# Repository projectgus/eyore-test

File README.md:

# Eyore-Test

A hardware design for running automated tests against the esp-open-rtos ESP8266-based software framework.

# Major Components

* 2x ESP-12E ESP8266 processor modules, to run tests on. Named A & B.
* 1x STM32F072C8 Cortex M0 microcontroller - acts as USB serial for programming & monitoring, also provides a "programmable peripheral" to test against.
* Host computer with esp-open-rtos source tree, including host test program (`test_runner.py`).

# Cost

Aim is for total BOM cost under $12US for small quantities, all inclusive.

# Functional Description

## Programming/Initialisation

STM32F072 acts as USB device (dual CDC ACM serial port). STM32 USART1 connects to ESP A's TX/RX pins, USART2 to ESP B TX/RX pins.

Other STM32 I/O pins are wired to drive RESET and GPIO0 on both ESP A & ESP B. This allows the STM32 to reset the ESPs & select either serial bootloading or normal operation.

The USB CDC interface provides a "NodeMCU-compatible" reset protocol that works with esptool.py - asserting DTR pulls down GPIO0, asserting RTS pulls down RESET, but asserting both DTR and RTS together does nothing.

## ESP A / ESP B Connections

These connections match the "dual" configuration mentioned in the esp-open-rtos test_setup docs. These allow the ESPs to interact with each other during tests.

This part of the test setup can be reproduced on a breadboard fairly easily.

ESP A & B have the following interconncted pins, all via 220 ohm resistors for short circuit protection:

ESP A | ESP B | Function
----- | ------  --------
2     | 2     |
4     | 4     |
5     | 5     |
12    | 12    |
13    | 15    | ESP UART RX/TX "swapped"
15    | 13    | ESP UART TX/RX "swapped"
14    | 14    |

Note that GPIOs on ESP A are also connected to the STM32.

## ESP A / STM32 Connections

To allow peripheral testing between ESP A and an independent microcontroller, some STM32 peripherals are connected to ESP A peripherals:

ESP A Interface | ESP GPIOs              | STM32 Interface | ESP Pins
--------------- | ---------------------- | ---------------- | ----------------
Software i2c    | 4, 5                   | I2C1             | PB6, PB7 [1]
HSPI            | 12-15                  | SPI1             | PA4-PA7
I2S Input       | 14(WS),13(BCK),12(DAT) | I2S1             | PA15, PB3, PB5
I2S Output      | 2(WS),3(DAT),14(CLK)   | N/A (bit-bang)   | PB11, PA9, PA4 [2]
SPI (flash intf)|                        | SPI2             | PB12..PB15 [3]
ADC (TOUT)      | TOUT                   | GPIO (bit-bang)  | PA0 & PB4 [4]

[1] I2C1 slave is the only STM32 interface enabled after reset, and is the protocol used for the ESP itself to configure the STM32 as a "programmable peripheral".

[2] ESP I2S output is not wired to a I2S peripheral on the STM32. However STM32 can bit-bang reading of the I2S output (at slow clock speeds).

[3] Not used due to hardware bug: On Rev 1.0 of eyore-test the SPI2 NSS pin (slave select) is wired to the CS line of the ESP module, which is the CS line for the ESP's SPI flash. The other SPI2 NSS pin is not connected in this revision.

[4] TOUT pin is connected directly to STM ADC pin PA0. TOUT is also connected to PB4 via an RC network, so PB4 can be used as a low-fi DAC, PWMing a voltage for the ADC to read.

## Programmable Peripheral Interface

As part of each test, ESP A can configure the STM32 peripherals via the I2C interface.

Actual I2C protocol/register details are TBD, likely to be incremental features.

# STM32 Firmware

STM32 has a USB DFU bootloader in ROM. "Flash" button and jumper are provided to access this bootloader on power-on. SWD port is also provided for external programming/debugging if necessary.

# Name

I've seen esp-open-rtos abbreviated to "e-o-r", and I tend to read that as "Eyore". :)

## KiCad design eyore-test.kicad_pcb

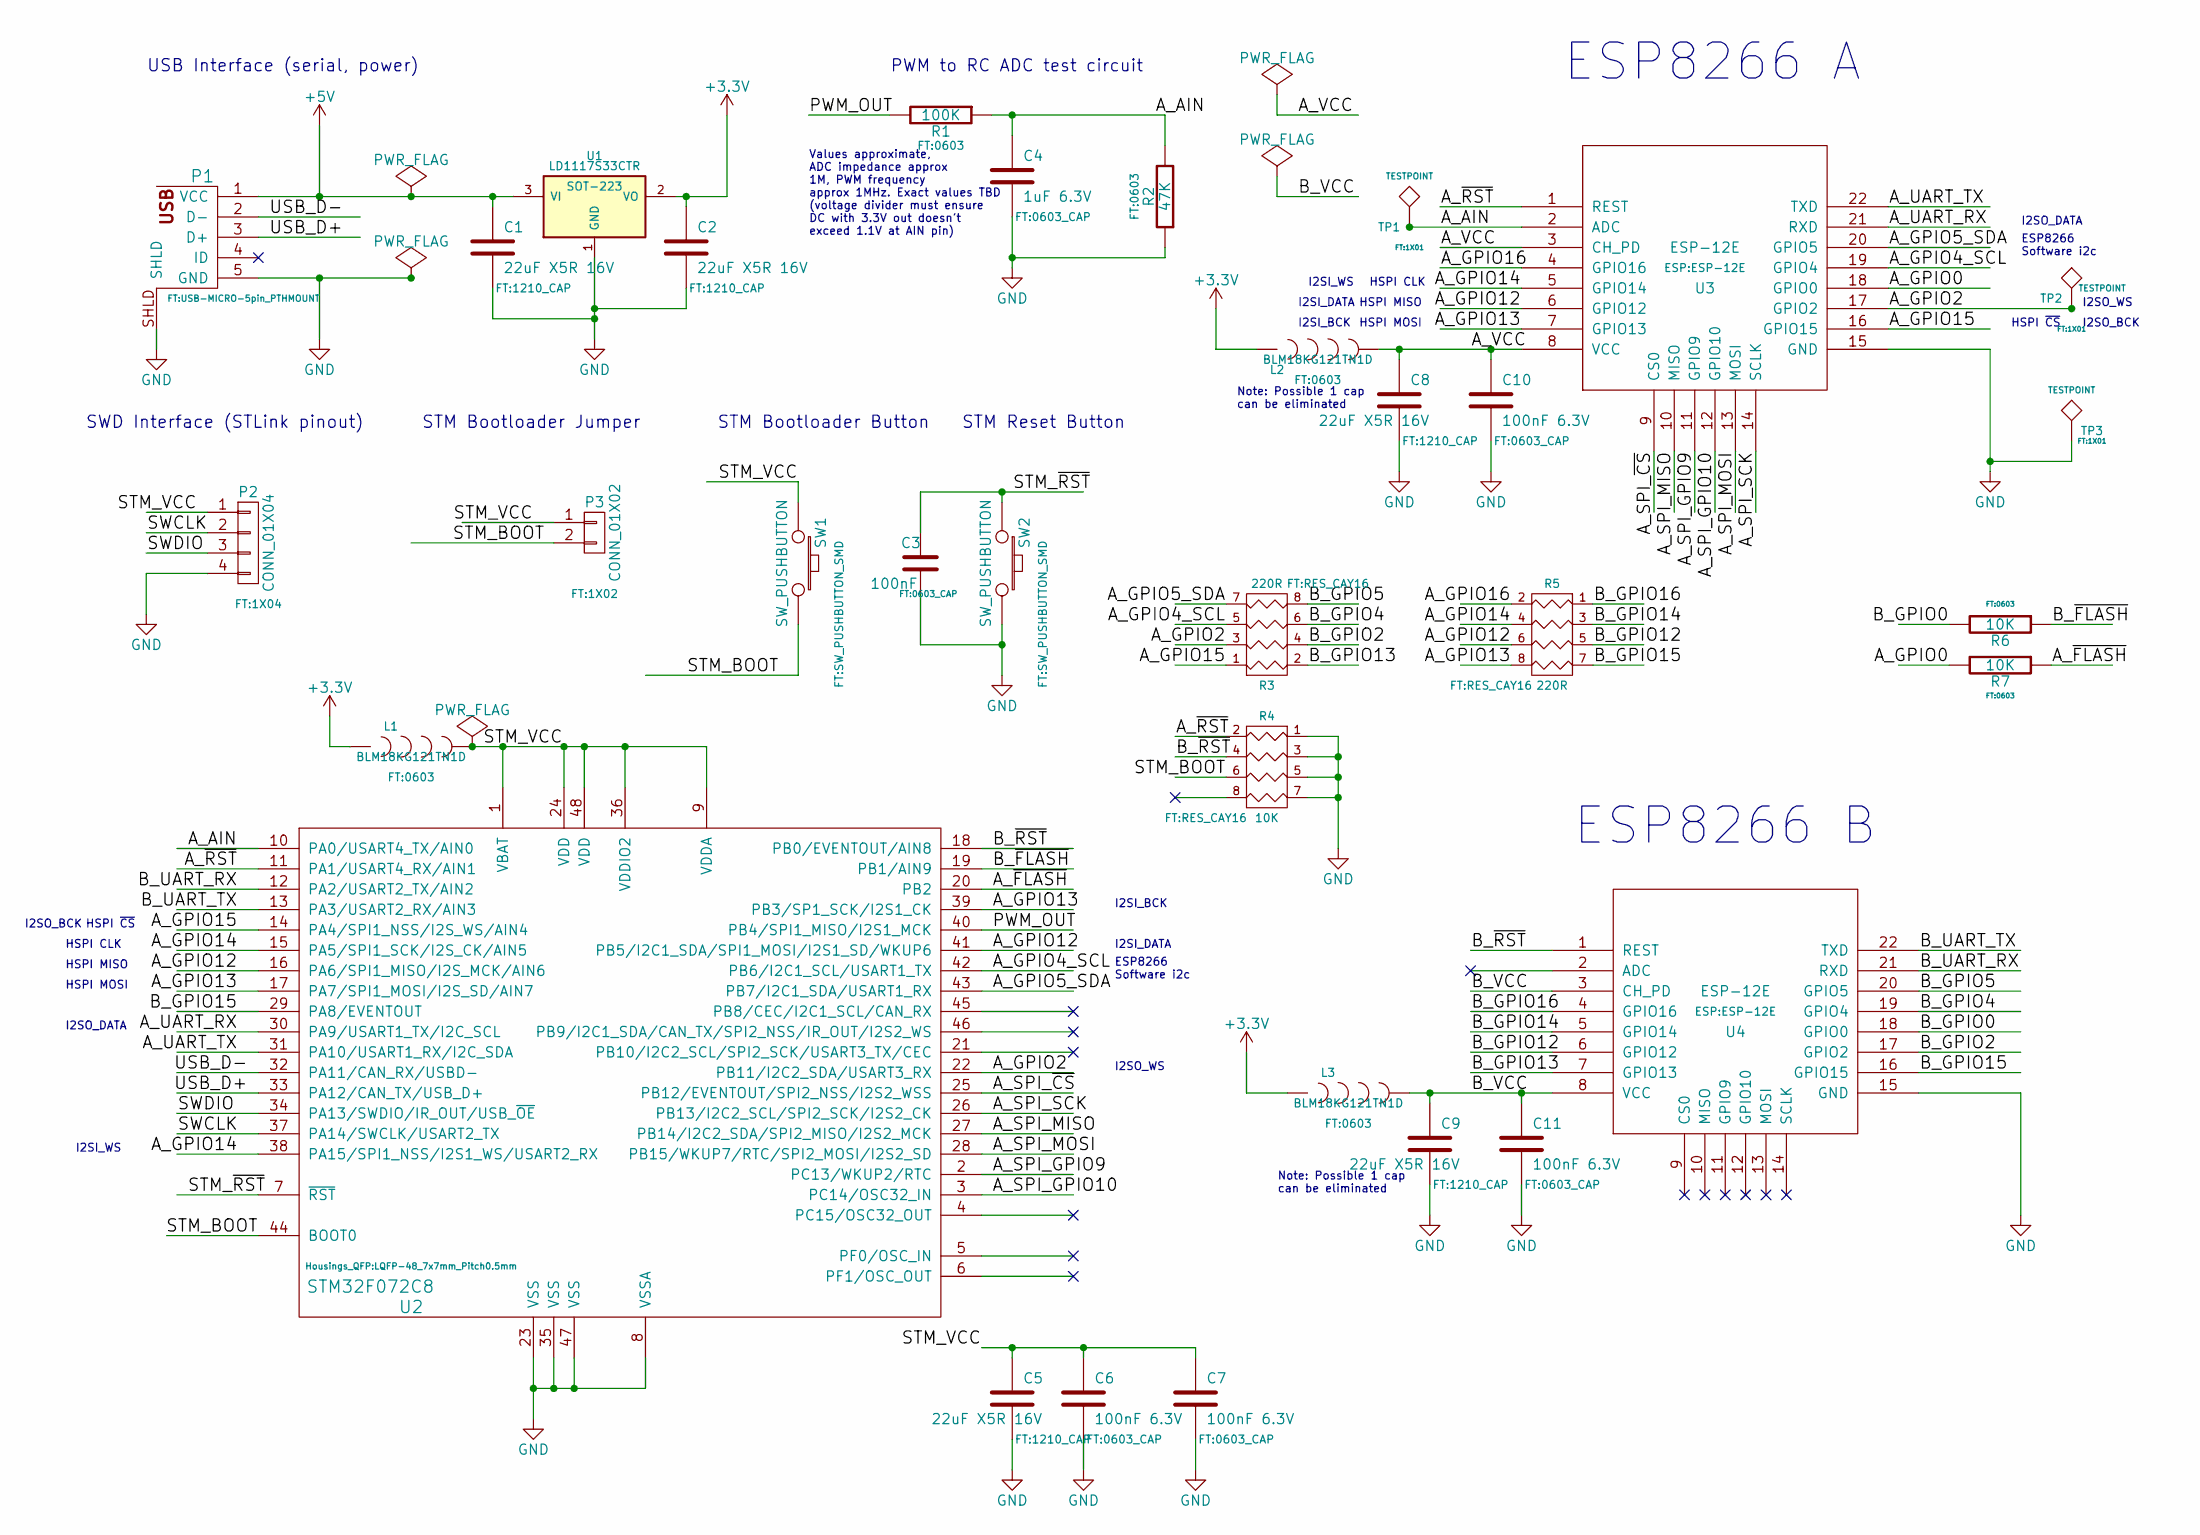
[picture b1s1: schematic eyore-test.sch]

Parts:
C1, C2, C5, C8, C9: 22uF X5R 16V; 1210_CAP
C3: 100nF; 0603_CAP
C4: 1uF 6.3V; 0603_CAP
C6, C7, C10, C11: 100nF 6.3V; 0603_CAP
L1, L2, L3: BLM18KG121TN1D; 0603
P1: USB_5PIN_SHELL; USB-MICRO-5pin_PTHMOUNT
P2: CONN_01X04; 1X04
P3: CONN_01X02; 1X02
R1: 100K; 0603
R2: 47K; 0603
R3, R5: 220R; RES_CAY16
R4: 10K; RES_CAY16
R6, R7: 10K; 0603
SW1, SW2: SW_PUSHBUTTON; SW_PUSHBUTTON_SMD
TP1, TP2, TP3: TESTPOINT; 1X01
U1: LD1117S33CTR; SOT-223
U2: STM32F072C8; LQFP-48_7x7mm_Pitch0.5mm
U3, U4: ESP-12E

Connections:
+3V3: C2.1, L1.1, L2.1, L3.1, U1.2 (VO)
+5V: C1.1, P1.1 (VCC), U1.3 (VI)
/A_AIN: C4.1, R1.1, R2.2, TP1.1, U2.10 (PA0/USART4_TX/AIN0), U3.2 (ADC)
/A_GPIO0: R7.2, U3.18 (GPIO0)
/A_GPIO2: R3.3 (P2), TP2.1, U2.22 (PB11/I2C2_SDA/USART3_RX), U3.17 (GPIO2)
/A_GPIO4_SCL: R3.5 (P3), U2.42 (PB6/I2C1_SCL/USART1_TX), U3.19 (GPIO4)
/A_GPIO5_SDA: R3.7 (P4), U2.43 (PB7/I2C1_SDA/USART1_RX), U3.20 (GPIO5)
/A_GPIO12: R5.6 (R3), U2.16 (PA6/SPI1_MISO/I2S_MCK/AIN6), U2.41 (PB5/I2C1_SDA/SPI1_MOSI/I2S1_SD/WKUP6), U3.6 (GPIO12)
/A_GPIO13: R5.8 (R4), U2.17 (PA7/SPI1_MOSI/I2S_SD/AIN7), U2.39 (PB3/SP1_SCK/I2S1_CK), U3.7 (GPIO13)
/A_GPIO14: R5.4 (R1), U2.15 (PA5/SPI1_SCK/I2S_CK/AIN5), U2.38 (PA15/SPI1_NSS/I2S1_WS/USART2_RX), U3.5 (GPIO14)
/A_GPIO15: R3.1, U2.14 (PA4/SPI1_NSS/I2S_WS/AIN4), U3.16 (GPIO15)
/A_GPIO16: R5.2 (R1), U3.4 (GPIO16)
/A_SPI_GPIO9: U2.2 (PC13/WKUP2/RTC), U3.11 (GPIO9)
/A_SPI_GPIO10: U2.3 (PC14/OSC32_IN), U3.12 (GPIO10)
/A_SPI_MISO: U2.27 (PB14/I2C2_SDA/SPI2_MISO/I2S2_MCK), U3.10 (MISO)
/A_SPI_MOSI: U2.28 (PB15/WKUP7/RTC/SPI2_MOSI/I2S2_SD), U3.13 (MOSI)
/A_SPI_SCK: U2.26 (PB13/I2C2_SCL/SPI2_SCK/I2S2_CK), U3.14 (SCLK)
/A_SPI_~CS: U2.25 (PB12/EVENTOUT/SPI2_NSS/I2S2_WSS), U3.9 (CS0)
/A_UART_RX: U2.30 (PA9/USART1_TX/I2C_SCL), U3.21 (RXD)
/A_UART_TX: U2.31 (PA10/USART1_RX/I2C_SDA), U3.22 (TXD)
/A_VCC: C8.1, C10.1, L2.2, U3.3 (CH_PD), U3.8 (VCC)
/A_~FLASH: R7.1, U2.20 (PB2)
/A_~RST: R4.2 (R1), U2.11 (PA1/USART4_RX/AIN1), U3.1 (REST)
/B_GPIO0: R6.2, U4.18 (GPIO0)
/B_GPIO2: R3.4 (R1), U4.17 (GPIO2)
/B_GPIO4: R3.6 (R3), U4.19 (GPIO4)
/B_GPIO5: R3.8 (R4), U4.20 (GPIO5)
/B_GPIO12: R5.5 (P3), U4.6 (GPIO12)
/B_GPIO13: R3.2 (R1), U4.7 (GPIO13)
/B_GPIO14: R5.3 (P2), U4.5 (GPIO14)
/B_GPIO15: R5.7 (P4), U2.29 (PA8/EVENTOUT), U4.16 (GPIO15)
/B_GPIO16: R5.1, U4.4 (GPIO16)
/B_UART_RX: U2.12 (PA2/USART2_TX/AIN2), U4.21 (RXD)
/B_UART_TX: U2.13 (PA3/USART2_RX/AIN3), U4.22 (TXD)
/B_VCC: C9.1, C11.1, L3.2, U4.3 (CH_PD), U4.8 (VCC)
/B_~FLASH: R6.1, U2.19 (PB1/AIN9)
/B_~RST: R4.4 (R1), U2.18 (PB0/EVENTOUT/AIN8), U4.1 (REST)
/PWM_OUT: R1.2, U2.40 (PB4/SPI1_MISO/I2S1_MCK)
/STM_BOOT: P3.2, R4.6 (R3), SW1.2, U2.44 (BOOT0)
/STM_VCC: C5.1, C6.1, C7.1, L1.2, P2.1, P3.1, SW1.1, U2.1 (VBAT), U2.9 (VDDA), U2.24 (VDD), U2.36 (VDDIO2), U2.48 (VDD)
/STM_~RST: C3.1, SW2.1, U2.7 (~RST)
/SWCLK: P2.2, U2.37 (PA14/SWCLK/USART2_TX)
/SWDIO: P2.3, U2.34 (PA13/SWDIO/IR_OUT/USB_~OE)
/USB_D+: P1.3 (D+), U2.33 (PA12/CAN_TX/USB_D+)
/USB_D-: P1.2 (D-), U2.32 (PA11/CAN_RX/USBD-)
GND: C1.2, C2.2, C3.2, C4.2, C5.2, C6.2, C7.2, C8.2, C9.2, C10.2, C11.2, P1.5 (GND), P1.SHLD, P2.4, R2.1, R4.1, R4.3 (P2), R4.5 (P3), R4.7 (P4), SW2.2, TP3.1, U1.1 (GND), U2.8 (VSSA), U2.23 (VSS), U2.35 (VSS), U2.47 (VSS), U3.15 (GND), U4.15 (GND)

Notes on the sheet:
SWD Interface (STLink pinout)
USB Interface (serial, power)
ESP8266 A
ESP8266 B
Note: Possible 1 cap can be eliminated
STM Bootloader Jumper
PWM to RC ADC test circuit
Values approximate, ADC impedance approx 1M, PWM frequency approx 1MHz. Exact values TBD (voltage divider must ensure DC with 3.3V out doesn't exceed 1.1V at AIN pin)
HSPI CLK
HSPI MISO
HSPI MOSI
HSPI ~CS
I2SI_DATA
I2SO_DATA
ESP8266 Software i2c
I2SI_WS
STM Bootloader Button
STM Reset Button
I2SO_BCK
I2SI_BCK
I2SI_BCK
I2SO_WS

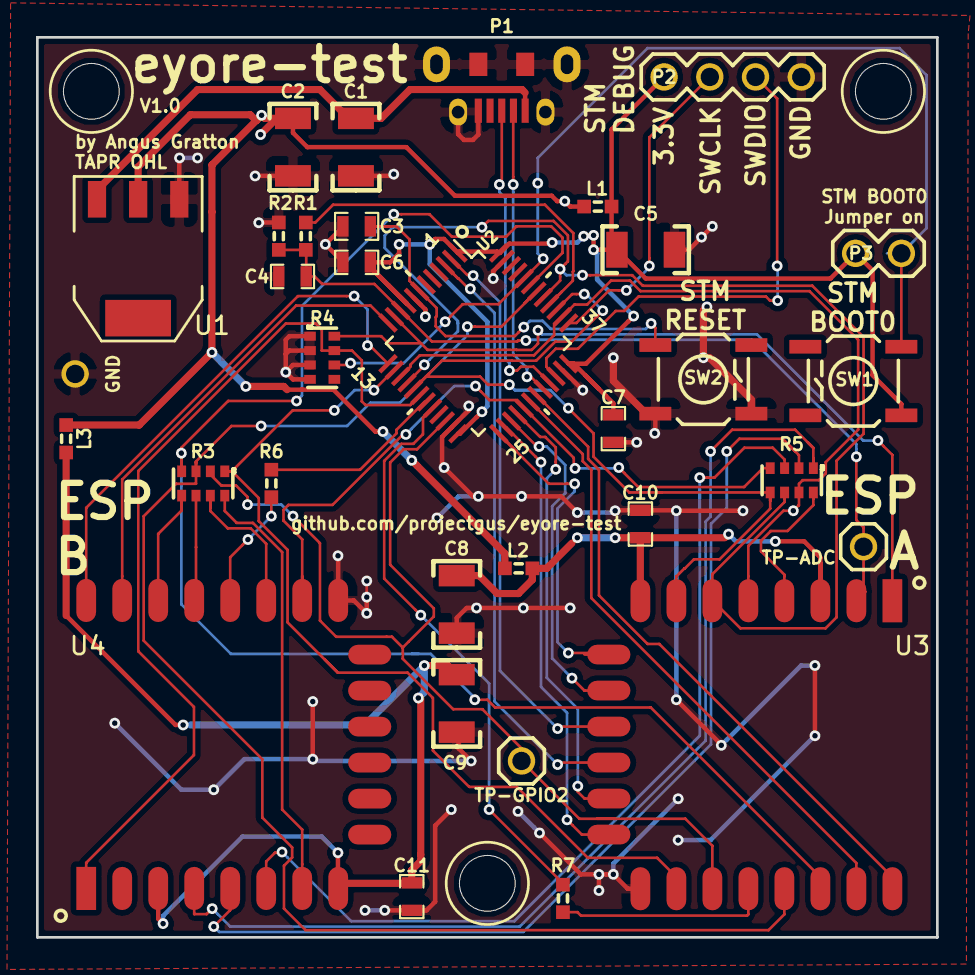
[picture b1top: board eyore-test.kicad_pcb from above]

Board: 2 copper layers, 50.0 x 50.0 mm, 36 parts (0 on the bottom side), 46 nets.

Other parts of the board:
1pin, 1pin#2, 1pin#3: VAL**; 1pin

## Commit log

2015-10-29 Initial commit, partial schematic
2015-10-29 Finished schematic draft
2015-10-29 Rename project to eyore-test
2015-10-29 Add README, schematic PDF
2015-10-29 More details about the test process
2015-10-29 More README detail
2015-11-10 Swap STM32F042K for larger STM32F042C, allow routing of ESP SPI port to second STM SPI
2015-11-15 Simplify UART wiring, general cleanup
2015-11-17 First cut at component layout
2015-12-01 Part routed, but I think approach was wrong
2015-12-06 Routed 4 layer version
2015-12-06 Rerouted as 2 layers
2015-12-06 Ready for V0.1 prototype
2015-12-07 V1.0 as ordered
2015-12-07 Move github URL to somewhere that won't be covered by capacitors
2016-03-01 Update README to match the actual boards that were made

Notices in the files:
eyore-test.sch:
TAPR Open Hardware License
Copyright (C) 2015 Angus Gratton
